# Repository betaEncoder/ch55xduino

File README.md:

# Ch55xduino: Small Devices Arduino for ch55x devices

**Getting started on the Ch55x the easy way. Forked from Sduino project, also based on 
ch554_sdcc project**

Ch55xduino is an Arduino-like programming API for the CH55X, a family of low-cost MCS51 USB MCU. The project tries to remove the difficulty of setting up a compiling environment. Users can simply write code in Arduino IDE and hit one button to flash the chip to get code running. No configuration or guesswork needed. 

CH551, CH552, CH554, may be the lowest part count system that works with Arduino. The minimal system only requires one chip, 2 decoupling capacitors, and one optional pull-up resistor. These features made it ideal for DIY projects. 

At this moment the project is still working-in-progress. Support most Arduino functions (Except pulse, shift, tone). Refer to examples in this repo for more info.

## Installation

Automatic IDE integration is supported via the
Arduino Boards Manager. This is the recommanded way of installation now. 

Start the Arduino-IDE. In *File->Preferences*, *Settings* tab, enter

> https://raw.githubusercontent.com/DeqingSun/ch55xduino/ch55xduino/package_ch55xduino_mcs51_index.json

as an *Additional Boards Manager URL*.

* Open *Tools->Board:...->Boards Manager*
* Find Ch55xduino by typing 'ch' into the search line
* Click on the list entry
* Click on *Install*.

Now you should find a new entry *CH55x Boards* in the list at
*Tools->Board:...*

* Choose *CH552 Board* from the list
* open the standard Blink example from *File->Examples->01. Basics->Blink*
* Change pin number in Blink example. For example, if you have LED on P3_0, you will write pin 30.
* compile it by hitting *Verify*
* If your board is never used with ch55xduino before, you need to make the ch55x chip enter bootloader mode. You need to disconnect USB and unpower ch55x, connect the pull-up resistor on D+ line (generally a 10K resistor between D+ and 5V, controlled by a push-button or adjacent pads). Then you connect USB. and hit *Upload*. Also, a blank new chip will enter the bootloader automatically.
* If you have used ch55xduino once and your code doesn't crash the USB subsystem, you can simply press *Upload*. Arduino and the firmware will kick the chip into the bootloader automatically.

### Installation without Github access

If you can not access github directly, use this link to a proxy instead.

> https://gh-proxy.deqing.workers.dev/raw.githubusercontent.com/DeqingSun/ch55xduino/playground/mirror/package_ch55xduino_mcs51_proxy_index.json

### USB and Serial upload

Ch55xduino supports both USB and Serial upload methods. If the USB port of the CH55x chip is connected to a host computer, the USB method is recommended.

It is also possible to upload via serial on UART1 of CH55x chips (except CH551). To set CH55x into bootloader mode automatically, you can connect RTS or DTR of a serial adaptor to an interrupt pin of CH55x with a capacitor, and add bootloader jumping code in the interrupt handler.

If you want to leave the bootloader, you may send the following bytes at 57600 baud. ```57 AB A2 01 00 01 A4```  

### Driver for windows

[Zadig](https://zadig.akeo.ie/) is the recommended tool to install drivers in Windows. The bootloader (4348,55E0) should be installed with WinUSB or libusb-win32 driver.

You can use USB Serial (CDC) driver for the default CDC USB stack (1209,C550). 

If you tried to emulate another type of USB device without changing the PID/VID, you may need to uninstall the device before installing a new driver.

### Permission for Linux

By default, Linux will not expose enough permission for Arduino to upload the code with the USB bootloader. Copy ```99-ch55xbl.rules``` in this repo to ```/etc/udev/rules.d/``` and restart your computer. Otherwise, the upload tool may not find the bootloader device.

## Reference board

There is a small CH552 breakout board design in the "pcb" folder. When fabricated with 1.6mm board thickness, some USB receptacle may be too loose for the PCB. Just add some tape behind the USB connector to increase the thickness.

The button footprint was designed for 6mm buttons, but 5mm one works too.

## Difference to regular Arduino

### Pin names:

Regular Arduino uses continuous numbers to code pins on AVR chips. In my opinion, it makes more sense since AVR uses letters as a port name. But MCS51 core uses numbers as port names. So CH55xduino's pins using the following rule. 

```PortNumber*10+PinNumber```

For example, P1.1 is 11, P3.2 is 32.

### Analog input:

CH552 has an 8-bit, 4 channel analog-to-digital converter on pin P1.1, P1.4, P1.5, and P3.2. So the input range is 0~255, not 1023.

By default, all pins on the MCS51 microcontrollers have internal pull-up resistors enabled. You may need to use ```pinMode``` to set the pin to ```INPUT``` to disable the pull-up resistor. 

There is no Analog Pin definition such as A0. Just use 11, 14, 15, or 32 for their analog input feature.

### No polymorph functions:

There is no free C++ compiler for MCS51 chip, we can not use polymorph functions. So you can not expect the compiler will choose a function according to the parameter's type. 

The biggest difference may be the ```Serial.print``` function. Here is what you should do in CH55xduino

| datatype | Print on USB | Println on USB | Print on UART0 | Println on UART0 |
|----------|--------------|----------------|----------------|------------------|
| int      | USBSerial\_print\_i(P) | USBSerial\_println\_i(P) | Serial0\_print\_i(P) | Serial0\_println\_i(P) |
| unsigned | USBSerial\_print\_u(P) | USBSerial\_println\_u(P) | Serial0\_print\_u(P) | Serial0\_println\_u(P) |
| float    | USBSerial\_print\_f(P) | USBSerial\_println\_f(P) | Serial0\_print\_f(P) | Serial0\_println\_f(P) |
| float with precision | USBSerial\_print\_f(P,Q) | USBSerial\_println\_f(P,Q) | Serial0\_print\_f(P,Q) | Serial0\_println\_f(P,Q) |
| char     | USBSerial\_print\_c(P) | USBSerial\_println\_c(P) | Serial0\_print\_c(P) | Serial0\_println\_c(P) |
| char * (str)  | USBSerial\_print\_s(P) | USBSerial\_println\_s(P) | Serial0\_print\_s(P) | Serial0\_println\_s(P) |
| char array with length | USBSerial\_print\_sn(P,Q) | USBSerial\_println\_sn(P,Q) | Serial0\_print\_sn(P,Q) | Serial0\_println\_sn(P,Q) |
| int with base | USBSerial\_print\_ub(P,Q) | USBSerial\_println\_ub(P,Q) | Serial0\_print\_ub(P,Q) | Serial0\_println\_ub(P,Q) |

They are defined in ```Arduino.h```.

### Memory model:

Unlike most modern architectures including AVR, MCS51 has 2 RAM regions, internal data memory, and external data memory. For CH552, the internal one is only 256 bytes, and the external one is 1024 bytes.

CH55xduino uses the default Small Model for SDCC memory models. The small memory model will allocate all variables in internal, directly addressable RAM by default. Variables stored in external RAM must be declared with the ```xdata``` or ```far``` keyword. 

CH55xduino also put the stack in internal RAM. So there isn't much space left for variables. If your variable doesn't need fast access, use ```__xdata``` when you declare it.  

For example, if you are trying to allocate a lot of space in internal RAM.

```uint8_t testArr[128];```

You will trigger an error. ```?ASlink-Error-Could not get 130 consecutive bytes in internal RAM for area DSEG.``` This can be avoided by using

```__xdata uint8_t testArr[128];```

For the default Arduino setting, 148 bytes are reserved for USB endpoints. There will be 876 bytes usable for external RAM.

You can see the memory mapping by opening the map and mem file generated along with the hex file.

#### Common Pitfalls when Using SDCC

Note that when some function is called from an interrupt service routine it should be preceded by a #pragma NOOVERLAY (if it is not reentrant) . A special note here, int (16 bit) and long (32 bit) integer division, multiplication & modulus operations are implemented using external support routines developed in ANSI-C, if an interrupt service routine needs to do any of these operations then the support routines (as mentioned in a following section) will have to recompiled using the --stack-auto option and the source file will need to be compiled using the --int-long-rent compiler option. [src](http://fivedots.coe.psu.ac.th/~cj/masd/resources/sdcc-doc/SDCCUdoc-11.html)

With SDCC, interrupt service routine function prototypes must be placed in the file that contains main ( ) in order for an vector for the interrupt to be placed in the the interrupt vector space.  It's acceptable to place the function prototype in a header file as long as the header file is included in the file that contains main ( ).  SDCC will not generate any warnings or errors if this is not done, but the vector will not be in place so the ISR will not be executed when the interrupt occurs. [src](https://www.silabs.com/community/mcu/8-bit/knowledge-base.entry.html/2007/11/16/common_pitfalls_when-E7zi)

### Reset Pins

Unlike AVR chips, CH55x will reset when the RST pin is High. The reset pin may be configured as an input pin. But such configuration requires modification of Configuration Information byte, which require an external tool to do so.

## Known issues

.

## Included libraries

Most parts of the Arduino core system and some Arduino libraries are already ported to C-syntax. The resulting API is still very close to the C++ version and porting an existing application is not hard. Refer to the examples that come with the libraries.

#### Communication

* SPI: Real hardware-SPI up to 12MHz.

#### Sensors

* TouchKey: Internal 6-channel capacitive touch module wrapper with an adaptive baseline algorithm.

## Compatibility with the Arduino world

Since there is no free C++ compiler for the MCS51, it is impossible to do a
full 1:1 port of the whole enviroment as is has been done for the STM32 and
the ESP8266.

This is not a drop-in replacement for an AVR, but thanks to some C
preprocessor magic the programming API is still very, very similar and it is
often enough to just move over the opening bracket of the class
instanciation statement and to replace the dot in a method call for an
underscore. Check the [migration
guide](https://tenbaht.github.io/sduino/api/migration/) for an overview.

## Supported Systems:

Arduino IDE versions 1.8.12 are tested, but
most versions >=1.6.6 should work.

* Windows: Tested on Windows 7 and XP.

* MacOS: Tested on 10.14.

* Linux: Tested on Ubuntu 20.04 LTS.

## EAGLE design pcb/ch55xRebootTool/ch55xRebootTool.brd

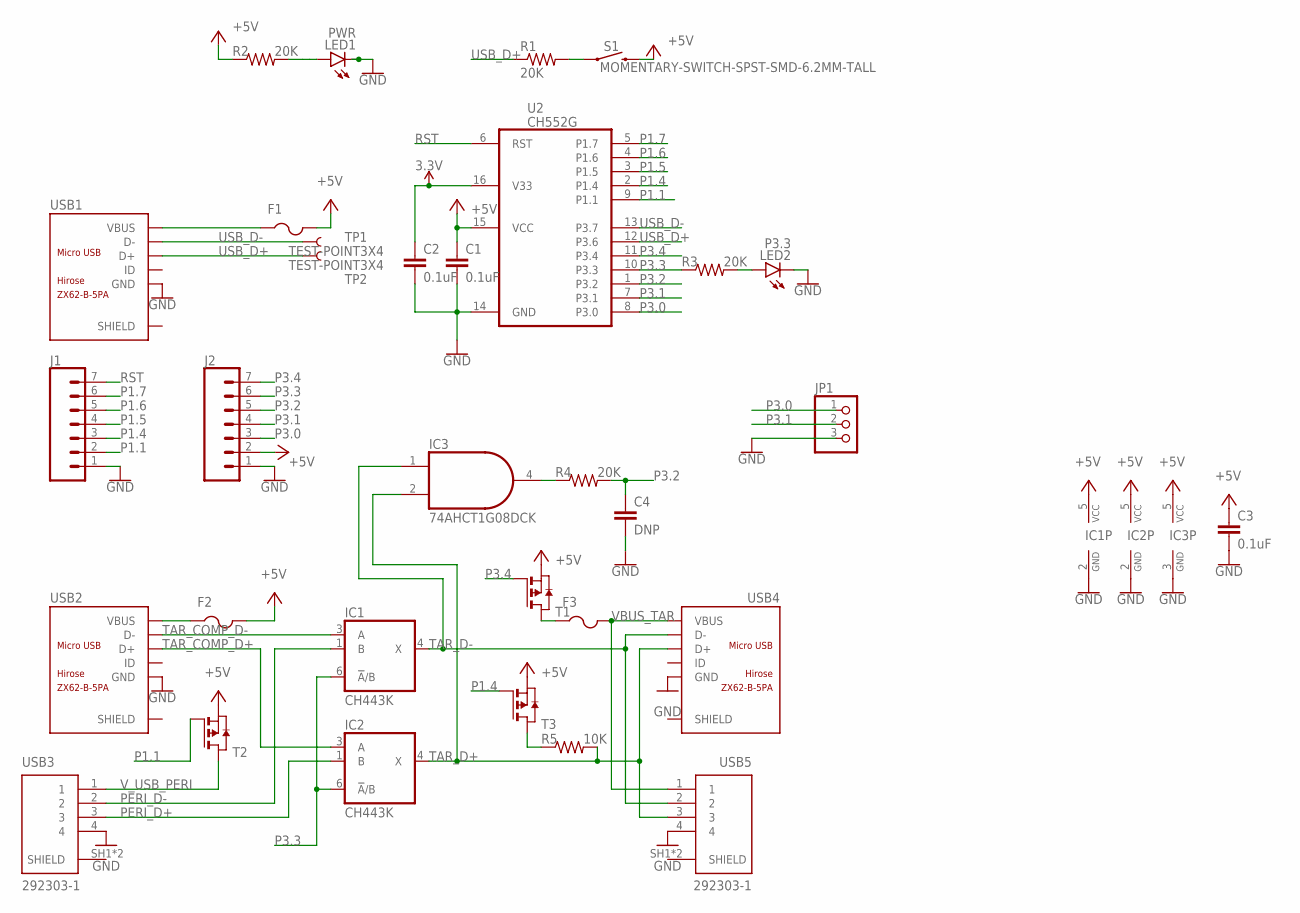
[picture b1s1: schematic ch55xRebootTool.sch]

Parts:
C1, C2, C3: 0.1uF; C0805K; LCSC C16834
C4: DNP; C0805K
F1, F2, F3: PTCFUSE-1206; R1206; LCSC C151162
IC1, IC2: CH443K; DCK_R-PDSO-G6; LCSC C125185
IC3: 74AHCT1G08DCK; SC70-5; LCSC C12493
J1, J2: CONN_07NO_SILK; 1X07_NO_SILK
JP1: PINHD-1X3; 1X03
LED1: PWR; GHI-BASICCOMPONENTS_0805-LED
LED2: P3.3; GHI-BASICCOMPONENTS_0805-LED
R1, R2, R3, R4: 20K; R0805
R5: 10K; R0805
S1: MOMENTARY-SWITCH-SPST-SMD-6.2MM-TALL; TACTILE_SWITCH_SMD_6.2MM_TALL
T1, T2, T3: PMOSSOT23; SOT-23
TP1, TP2: TEST-POINT3X4; PAD.03X.04
U2: CH552G; MY_IC_SO16; LCSC C111292
USB1, USB2, USB4: ZX62-B-5PA; MICRO-USB5+6P-SMD-0.65-AB; LCSC C10418
USB3, USB5: 292303-1; LCSC C2345

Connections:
3.3V: C2.1, U2.16 (V33)
+5V: C1.1, C3.1, F1.2, F2.2, IC1.5 (VCC), IC2.5 (VCC), IC3.5 (VCC), J2.2, R2.1, S1.B2 (2), T1.2 (S), T2.2 (S), T3.2 (S), U2.15 (VCC)
GND: C1.2, C2.2, C3.2, C4.2, IC1.2 (GND), IC2.2 (GND), IC3.3 (GND), J1.1, J2.1, JP1.3, LED1.K, LED2.K, U2.14 (GND), USB1.5 (GND), USB2.5 (GND), USB3.4, USB4.5 (GND), USB5.4
unnamed: R1.2, S1.A2 (1)
unnamed: LED2.A, R3.2
unnamed: LED1.A, R2.2
unnamed: IC3.4 (O), R4.1
unnamed: F3.1, T1.1 (D)
unnamed: R5.1, T3.1 (D)
P1.1: J1.2, T2.3 (G), U2.9 (P1.1)
P1.4: J1.3, T3.3 (G), U2.2 (P1.4)
P1.5: J1.4, U2.3 (P1.5)
P1.6: J1.5, U2.4 (P1.6)
P1.7: J1.6, U2.5 (P1.7)
P3.0: J2.3, JP1.1, U2.8 (P3.0)
P3.1: J2.4, JP1.2, U2.7 (P3.1)
P3.2: C4.1, J2.5, R4.2, U2.1 (P3.2)
P3.3: IC1.6 (!A!/B), IC2.6 (!A!/B), J2.6, R3.1, U2.10 (P3.3)
P3.4: J2.7, T1.3 (G), U2.11 (P3.4)
PERI_D+: IC2.1 (B), USB3.3
PERI_D-: IC1.1 (B), USB3.2
RST: J1.7, U2.6 (RST)
SHIELD: USB3.SH1 (SHIELD), USB3.SH2 (SHIELD), USB5.SH1 (SHIELD), USB5.SH2 (SHIELD)
TAR_COMP_D+: IC2.3 (A), USB2.3 (D+)
TAR_COMP_D-: IC1.3 (A), USB2.2 (D-)
TAR_D+: IC2.4 (X), IC3.2 (I1), R5.2, USB4.3 (D+), USB5.3
TAR_D-: IC1.4 (X), IC3.1 (I0), USB4.2 (D-), USB5.2
USB_D+: R1.1, TP2.P$1, U2.12 (P3.6), USB1.3 (D+)
USB_D-: TP1.P$1, U2.13 (P3.7), USB1.2 (D-)
VBUS: F1.1, USB1.1 (VBUS)
VBUS_COMP: F2.1, USB2.1 (VBUS)
VBUS_TAR: F3.2, USB4.1 (VBUS), USB5.1
V_USB_PERI: T2.1 (D), USB3.1

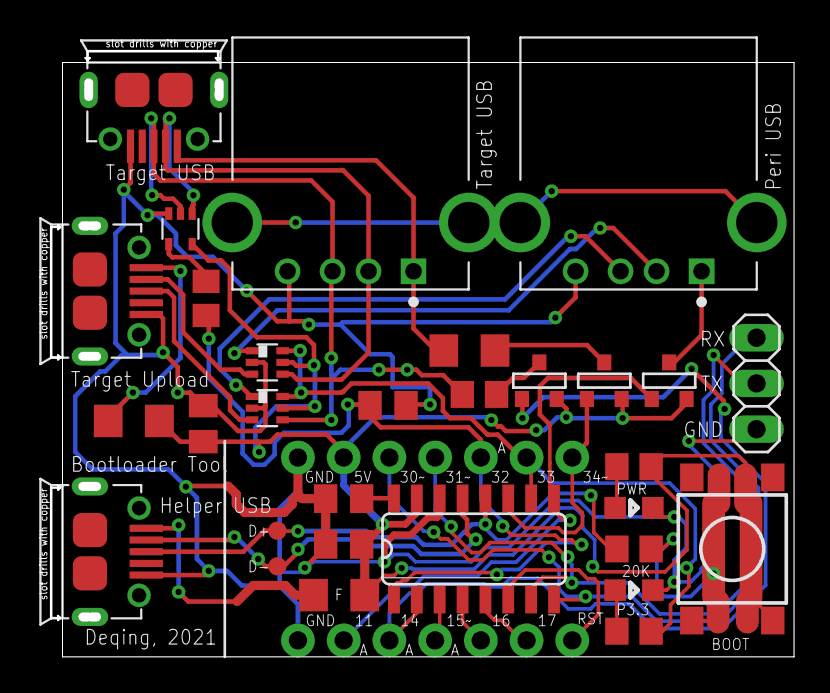
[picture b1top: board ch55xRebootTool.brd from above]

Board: 2 copper layers, 41.3 x 33.7 mm, 32 parts (0 on the bottom side), 33 nets.

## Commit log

2021-01-04 get started in MSD code
2021-01-04 SCSI_TEST_UNIT_READY pass
2021-01-04 SCSI_INQUIRY OK
2021-01-04 SCSI_ALLOW_MEDIUM_REMOVAL OK
2021-01-04 SCSI_REQUEST_SENSE OK
2021-01-04 SCSI_READ_CAPACITY10 OK
2021-01-04 SCSI_MODE_SENSE6 OK
2021-01-04 fix SCSI_READ_CAPACITY10
2021-01-04 SCSI_READ10 start to work without meaningful data
2021-01-04 change pid
2021-01-04 SCSI_READ_FORMAT_CAPACITIES OK
2021-01-04 add values
2021-01-04 SCSI_START_STOP_UNIT SCSI_MODE_SENSE10 SCSI_FORMAT_UNIT added not tested
2021-01-04 disk appears
2021-01-05 fat readable
2021-01-05 readable on mac not on windows
2021-01-05 files readable
2021-01-05 optimize by remove ptr
2021-01-06 dynamic root dir start to work.
2021-01-06 optimize a bit
2021-01-06 remove debug
2021-01-06 fix root bug
2021-01-06 fat and response work
2021-01-06 fix mac recognition
2021-01-06 change name
2021-01-06 fat support long file
2021-01-06 remove non-ascii
2021-01-06 update time
2021-01-06 increase fat table to make use of 8M space.
2021-01-06 update long file
2021-01-07 fix 3rd file issue.
2021-01-08 remove old files
2021-01-08 add bootloader tool
2021-01-09 add SCSI_Write10_Cmd
2021-01-09 remove read only disk setting
2021-01-10 use Bad cluster for all free space. This works well in XP.
2021-01-10 change _File_Entry
2021-01-10 Add LED control from file.
2021-01-10 add dataflash bin
2021-01-10 add mass storage example
2021-01-10 add tool
2021-01-26 Update comment on DAP example
2021-01-26 Update comment for CMSIS_DAP example
2021-02-05 start to add CH549
2021-02-11 add mcu parameter
2021-02-11 add ch549 header
2021-02-11 add condition to get ch549 compile
2021-02-11 adjust timing, reboot not working yet
2021-02-11 can blink
2021-02-11 add basic support for CH549
2021-02-19 CH559 can upload code
2021-02-19 can access IO
2021-02-19 adjust clock
2021-02-19 fix endianness issue for CH559
2021-02-20 update comment for CMSIS_DAP
2021-02-20 duplicate micro and millis from 24M to 56M as temp code.
2021-02-20 reduce R4 to remove offset
2021-02-20 change spacing
2021-02-20 micros work for 56M
2021-02-21 update millis for 56M
2021-02-21 add analogRead for CH559
2021-02-21 add pwm write
2021-02-21 add ch559 support
2021-02-22 add script for packing code
2021-03-02 add some parts for reboot tool
2021-03-03 move host example
2021-03-07 update HID report
2021-03-13 update board
2021-03-16 update driver instruction
2021-04-28 add basic reboot tool
2021-05-26 fix marco in WS2812
2021-05-26 fix macro error in WS2812
2021-05-27 skelton added and descriptors are modified
2021-05-27 define button constant
2021-05-29 wheel support
2021-05-29 Functions are replaced for mouse
2021-05-29 fix descriptor error and it works 3 buttons
2021-05-29 cursol xy move function added
2021-05-29 scroll function added
2021-05-29 fix serial string descriptor
2021-05-29 little refactoring
2021-06-05 USB mouse and keyboard device support
2021-06-06 generic hid transfer support
2021-06-06 readme is added
2021-06-06 credit is modified
2021-06-06 little note added
2021-06-08 mouse, keyboard and vendor specific io device support

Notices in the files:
parts and their libraries:
SparkFun-Connectors: Licensing: Creative Commons ShareAlike 4.0 International - https://creativecommons.org/licenses/by-sa/4.0
